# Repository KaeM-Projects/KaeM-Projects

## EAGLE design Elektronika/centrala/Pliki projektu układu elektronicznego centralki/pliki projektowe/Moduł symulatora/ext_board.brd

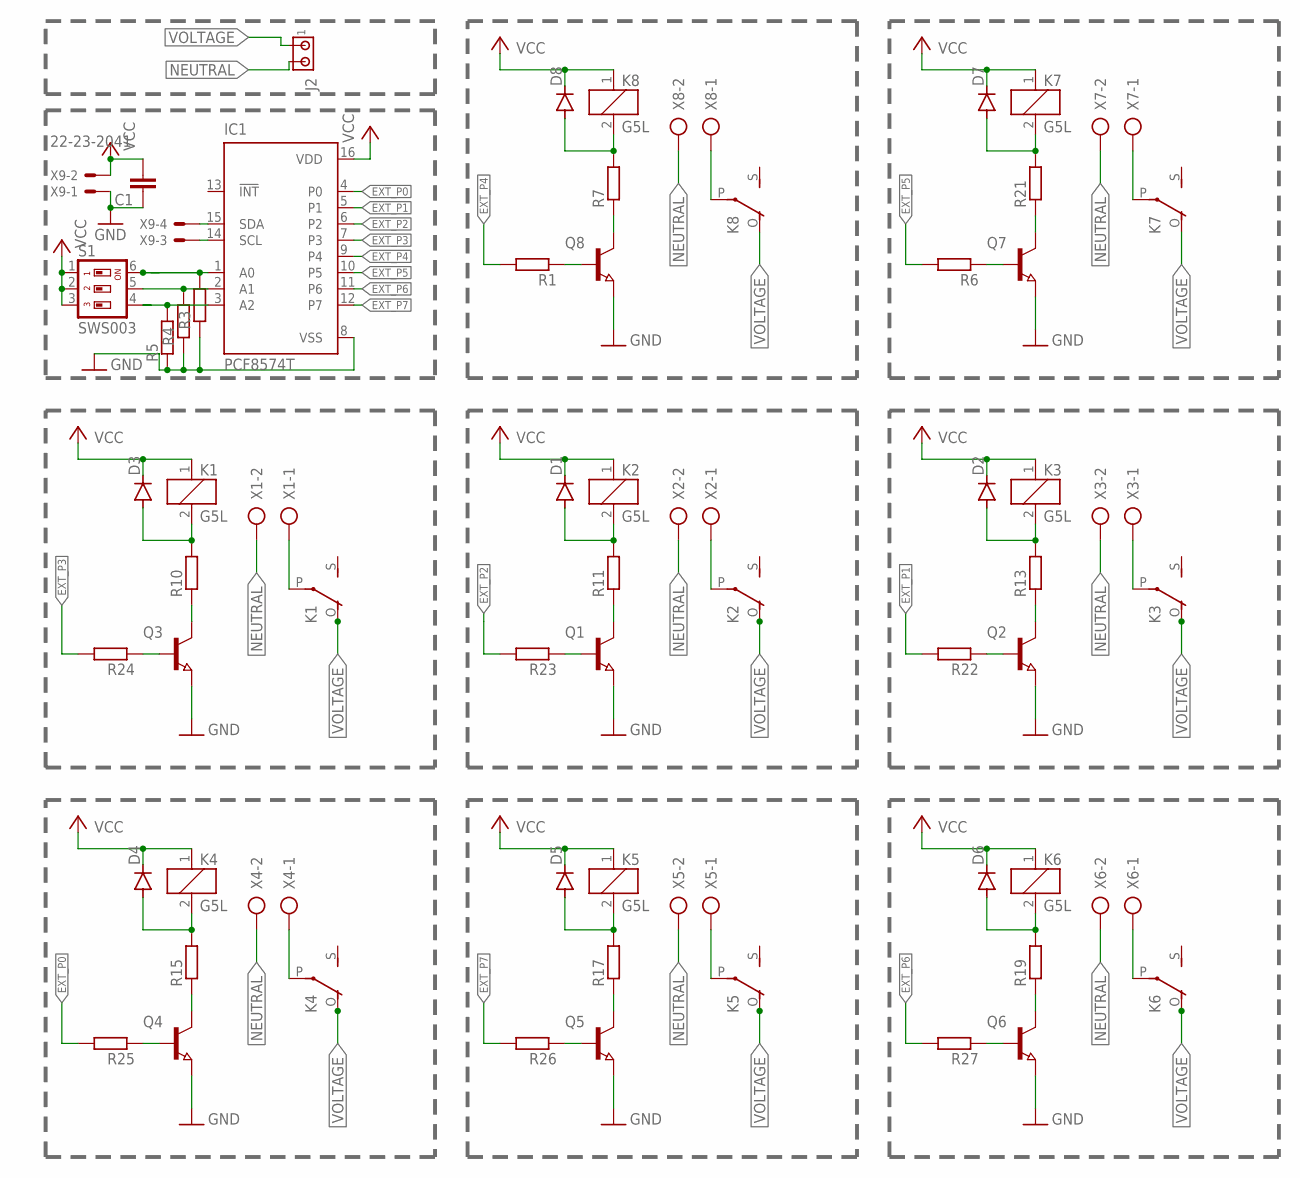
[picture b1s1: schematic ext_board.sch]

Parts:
C1: C-EUC2012; C2012
D1, D2, D3, D4, D5, D6, D7, D8: DIODE-DO-214AC; DO-214AC
IC1: PCF8574T; SO16W
J2: MTA02-156; 1X2MTA
K1, K2, K3, K4, K5, K6, K7, K8: G5L; G5LE
Q1, Q2, Q3, Q4, Q5, Q6, Q7, Q8: NPN-TRANSISTOR_SOT23; SOT23
R1, R6, R22, R23, R24, R25, R26, R27: R-EU_R2010; R2010
R3, R4, R5, R7, R10, R11, R13, R15, R17, R19, R21: R-EU_M2012; M2012
S1: SWS003; SMS-003
X1, X2, X3, X4, X5, X6, X7, X8: AK300/2
X9: 22-23-2041

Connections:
EXT_P0: IC1.4 (P0), R25.2
EXT_P1: IC1.5 (P1), R22.2
EXT_P2: IC1.6 (P2), R23.2
EXT_P3: IC1.7 (P3), R24.2
EXT_P4: IC1.9 (P4), R1.2
EXT_P5: IC1.10 (P5), R6.2
EXT_P6: IC1.11 (P6), R27.2
EXT_P7: IC1.12 (P7), R26.2
GND: C1.1, IC1.8 (VSS), Q1.2 (E), Q2.2 (E), Q3.2 (E), Q4.2 (E), Q5.2 (E), Q6.2 (E), Q7.2 (E), Q8.2 (E), R3.1, R4.1, R5.1, X9.1
unnamed: IC1.2 (A1), R4.2, S1.5
unnamed: IC1.3 (A2), R5.2, S1.4
unnamed: IC1.1 (A0), R3.2, S1.6
unnamed: Q3.1 (B), R24.1
unnamed: Q1.1 (B), R23.1
unnamed: D3.A, K1.2, R10.2
unnamed: Q3.3 (C), R10.1
unnamed: K1.P, X1.1
unnamed: D1.A, K2.2, R11.2
unnamed: Q1.3 (C), R11.1
unnamed: K2.P, X2.1
unnamed: Q2.1 (B), R22.1
unnamed: D2.A, K3.2, R13.2
unnamed: Q2.3 (C), R13.1
unnamed: K3.P, X3.1
unnamed: Q4.1 (B), R25.1
unnamed: D4.A, K4.2, R15.2
unnamed: Q4.3 (C), R15.1
unnamed: K4.P, X4.1
unnamed: Q5.1 (B), R26.1
unnamed: D5.A, K5.2, R17.2
unnamed: Q5.3 (C), R17.1
unnamed: K5.P, X5.1
unnamed: Q6.1 (B), R27.1
unnamed: D6.A, K6.2, R19.2
unnamed: Q6.3 (C), R19.1
unnamed: K6.P, X6.1
unnamed: Q7.1 (B), R6.1
unnamed: D7.A, K7.2, R21.2
unnamed: Q7.3 (C), R21.1
unnamed: K7.P, X7.1
unnamed: Q8.1 (B), R1.1
unnamed: D8.A, K8.2, R7.2
unnamed: Q8.3 (C), R7.1
unnamed: K8.P, X8.1
NEUTRAL: J2.2, X1.2, X2.2, X3.2, X4.2, X5.2, X6.2, X7.2, X8.2
SCL: IC1.14 (SCL), X9.3
SDA: IC1.15 (SDA), X9.4
VCC: C1.2, D1.C, D2.C, D3.C, D4.C, D5.C, D6.C, D7.C, D8.C, IC1.16 (VDD), K1.1, K2.1, K3.1, K4.1, K5.1, K6.1, K7.1, K8.1, S1.1, S1.2, S1.3, X9.2
VOLTAGE: J2.1, K1.O, K2.O, K3.O, K4.O, K5.O, K6.O, K7.O, K8.O

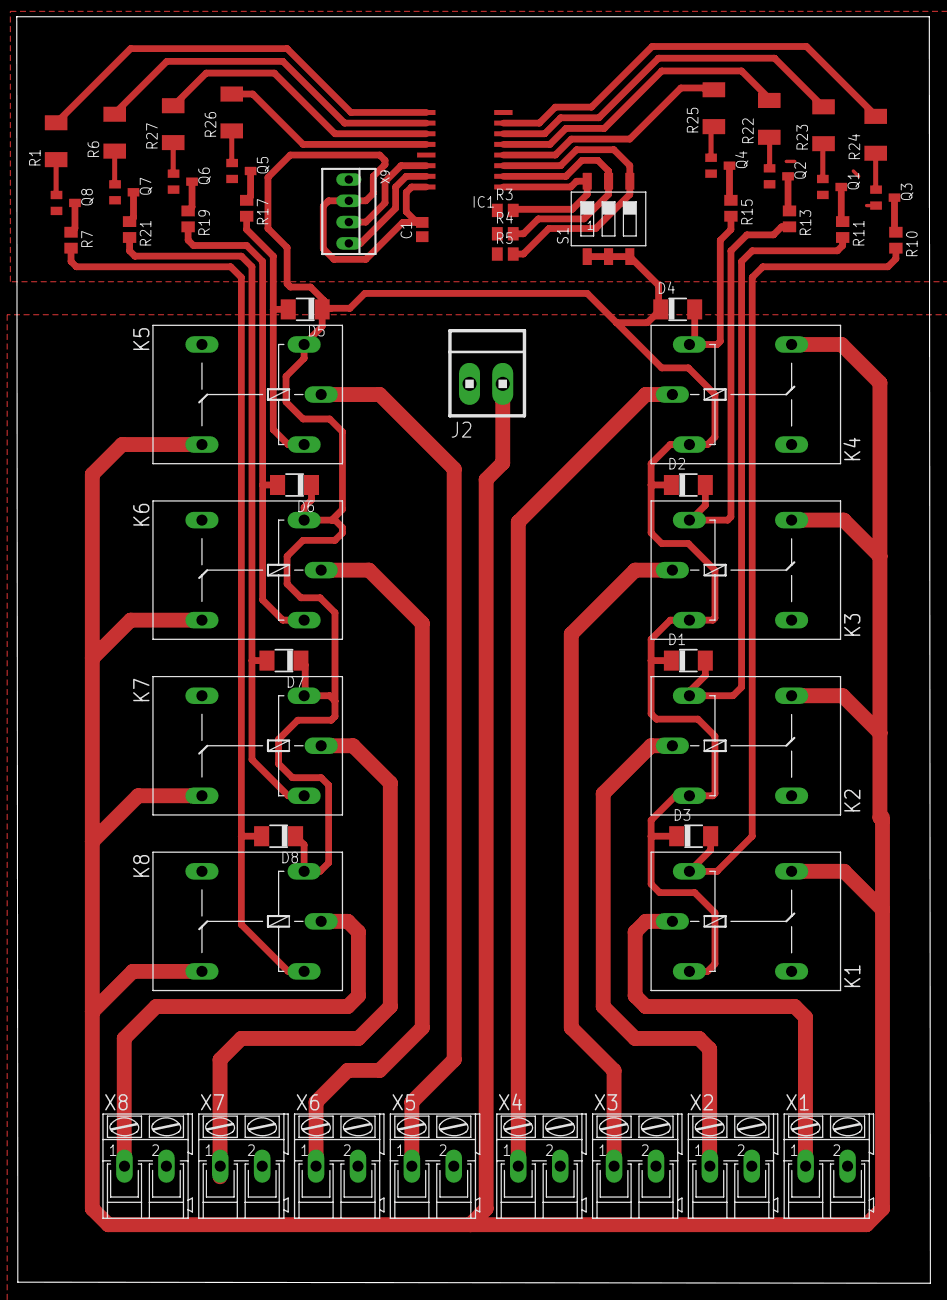
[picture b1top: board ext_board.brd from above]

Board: 2 copper layers, 109.0 x 151.1 mm, 56 parts (0 on the bottom side), 49 nets.

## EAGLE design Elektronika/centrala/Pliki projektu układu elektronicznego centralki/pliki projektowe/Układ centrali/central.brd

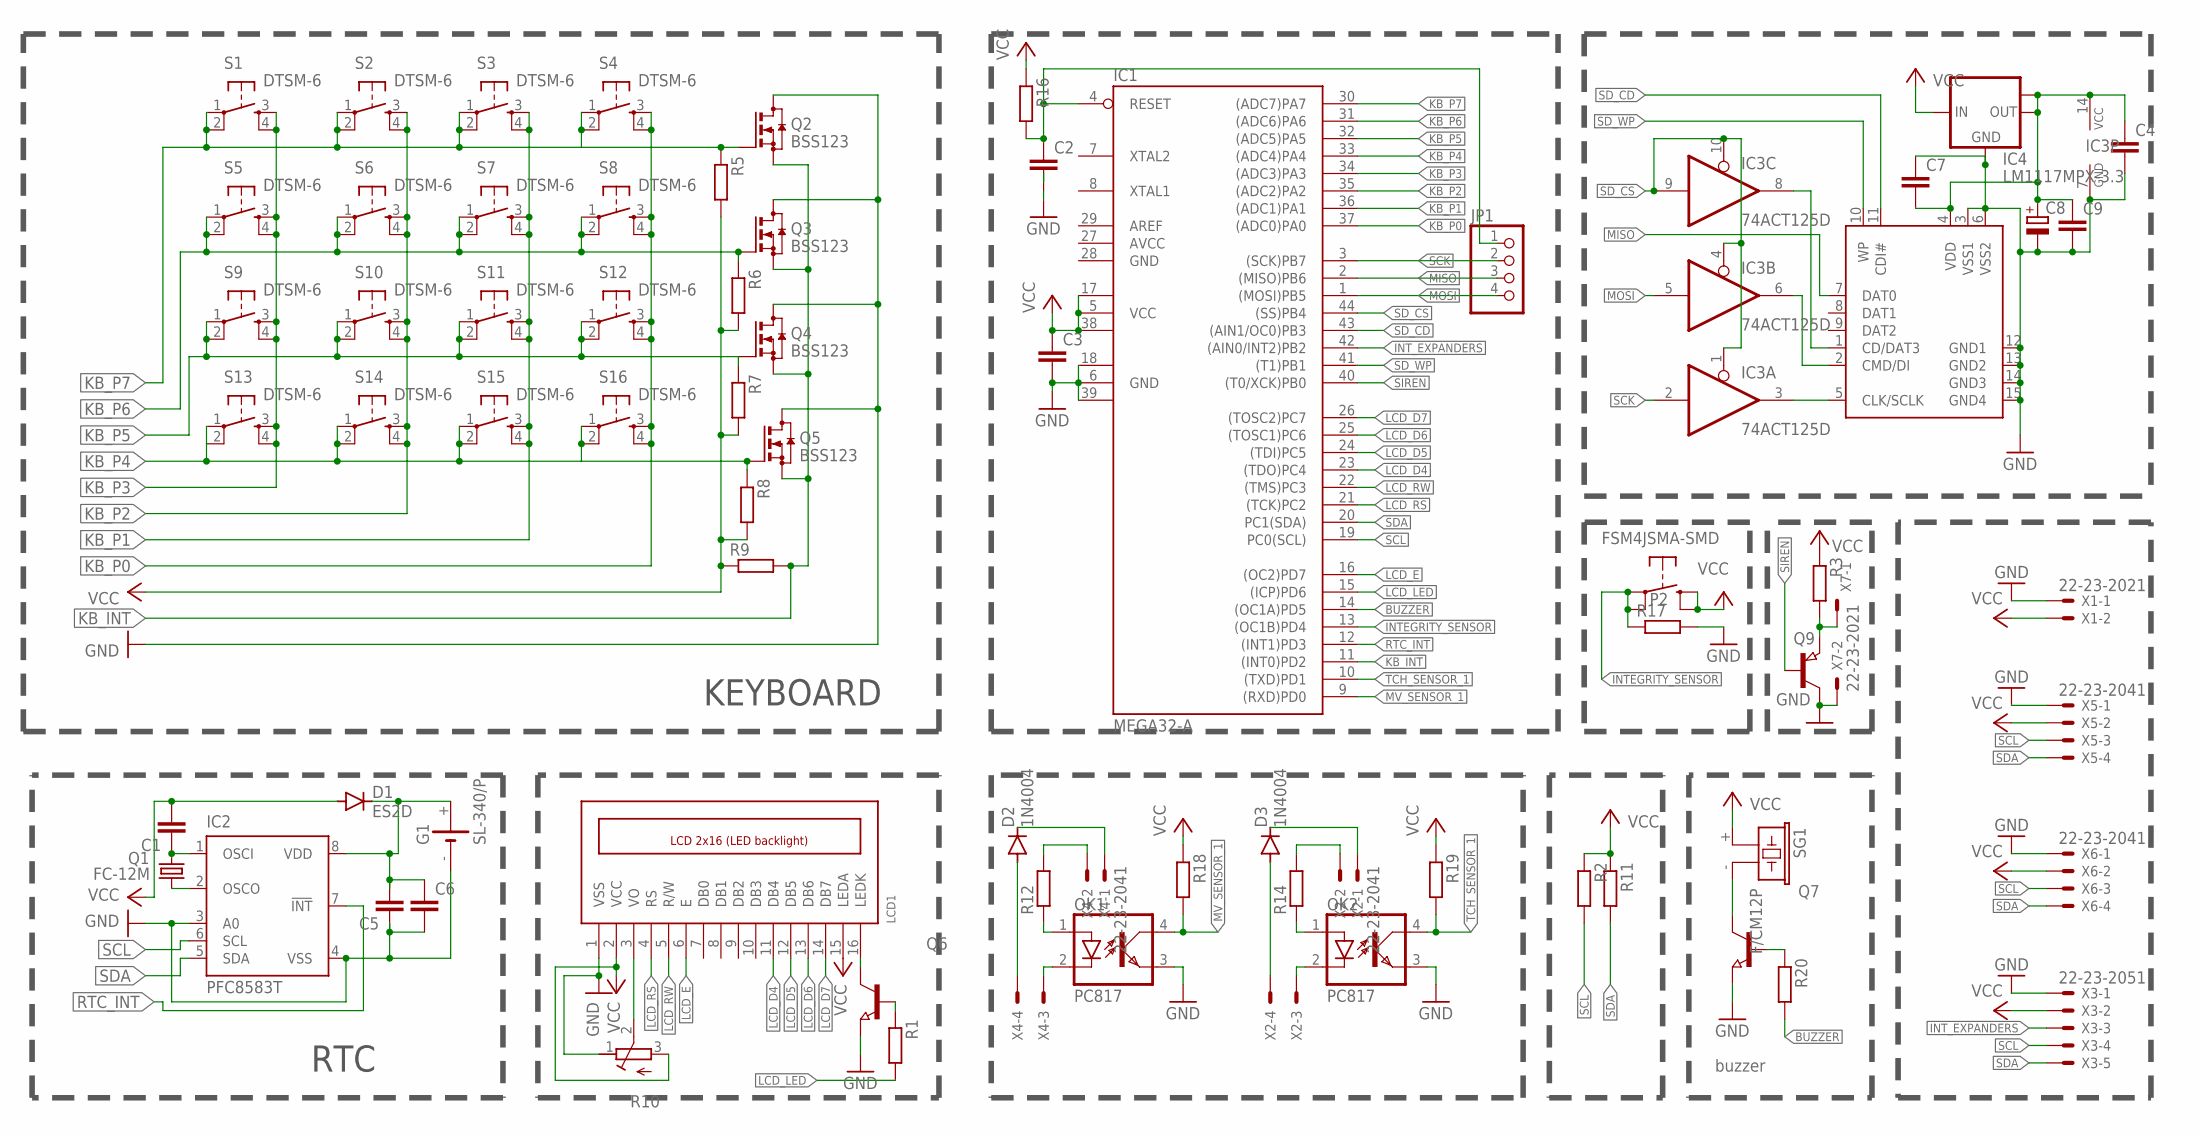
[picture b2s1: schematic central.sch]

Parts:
C1, C2, C3, C5: C-EUC2012; C2012
C4, C6, C7, C9: C-EUC4532; C4532
C8: CPOL-EUE1.8-4; E1,8-4
D1: ES2D; SMB
D2, D3: 1N4004; DO41-10
G1: SL-340/P; BEL/P
IC1: MEGA32-A; TQFP44
IC2: PFC8583T; SO8-7_5
IC3: 74ACT125D; SO14
IC4: LM1117MPX-3.3; SOT223
JP1: PINHD-1X4/90; 1X04/90
LCD1: LCD_2X16_SIL; HY-1602F
OK1, OK2: PC817; DIL04
P2: FSM4JSMA-SMD
Q1: FC-12M
Q2, Q3, Q4, Q5: BSS123; SOT23
Q6, Q7: NPN-TRANSISTOR_SOT23; SOT23
Q9: PNP-TRANSISTOR_SOT23; SOT23
R1, R2, R3, R5, R6, R7, R8, R9, R11, R16, R17, R18, R19, R20: R-EU_M3216; M3216
R10: R-TRIMM3314G; RTRIM3314G
R12, R14: R-EU_0309/12; 0309/12
S1, S2, S3, S4, S5, S6, S7, S8, S9, S10, S11, S12, S13, S14, S15, S16: DTSM-6
SG1: F/CM12P
U$1: SDCARDVAR1; SDCMF-10915W010
X1, X7: 22-23-2021
X2, X4, X5, X6: 22-23-2041
X3: 22-23-2051

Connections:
AVCC: IC1.27 (AVCC)
BUZZER: IC1.14 ((OC1A)PD5), R20.2
GND: C2.2, C3.2, C4.2, C5.1, C6.2, C7.1, C8.-, C9.2, G1.-, IC1.6 (GND), IC1.18 (GND1), IC1.28 (GND), IC1.39 (GND2), IC2.3 (A0), IC2.4 (VSS), IC3.7 (GND), IC4.1 (GND), LCD1.1 (VSS), OK1.3 (EMIT), OK2.3 (EMIT), Q2.3 (D), Q3.3 (D), Q4.3 (D), Q5.3 (D), Q6.2 (E), Q7.2 (E), Q9.3 (C), R10.1 (E), R17.2, U$1.3 (VSS1), U$1.6 (VSS2), U$1.12 (GND1), U$1.13 (GND2), U$1.14 (GND3), U$1.15 (GND4), X1.1, X3.1, X5.1, X6.1, X7.2
INTEGRITY_SENSOR: IC1.13 ((OC1B)PD4), P2.P$1, P2.P$2, R17.1
INT_EXPANDERS: IC1.42 ((AIN0/INT2)PB2), X3.3
KB_INT: IC1.11 ((INT0)PD2), Q2.2 (S), Q3.2 (S), Q4.2 (S), Q5.2 (S), R9.2
KB_P0: IC1.37 ((ADC0)PA0), S4.3, S4.4, S8.3, S8.4, S12.3, S12.4, S16.3, S16.4
KB_P1: IC1.36 ((ADC1)PA1), S3.3, S3.4, S7.3, S7.4, S11.3, S11.4, S15.3, S15.4
KB_P2: IC1.35 ((ADC2)PA2), S2.3, S2.4, S6.3, S6.4, S10.3, S10.4, S14.3, S14.4
KB_P3: IC1.34 ((ADC3)PA3), S1.3, S1.4, S5.3, S5.4, S9.3, S9.4, S13.3, S13.4
KB_P4: IC1.33 ((ADC4)PA4), Q5.1 (G), R8.1, S13.1, S13.2, S14.1, S14.2, S15.1, S15.2, S16.1, S16.2
KB_P5: IC1.32 ((ADC5)PA5), Q4.1 (G), R7.1, S9.1, S9.2, S10.1, S10.2, S11.1, S11.2, S12.1, S12.2
KB_P6: IC1.31 ((ADC6)PA6), Q3.1 (G), R6.1, S5.1, S5.2, S6.1, S6.2, S7.1, S7.2, S8.1, S8.2
KB_P7: IC1.30 ((ADC7)PA7), Q2.1 (G), R5.1, S1.1, S1.2, S2.1, S2.2, S3.1, S3.2, S4.1, S4.2
LCD_D4: IC1.23 ((TDO)PC4), LCD1.11 (DB4)
LCD_D5: IC1.24 ((TDI)PC5), LCD1.12 (DB5)
LCD_D6: IC1.25 ((TOSC1)PC6), LCD1.13 (DB6)
LCD_D7: IC1.26 ((TOSC2)PC7), LCD1.14 (DB7)
LCD_E: IC1.16 ((OC2)PD7), LCD1.6 (E)
LCD_LED: IC1.15 ((ICP)PD6), R1.2
LCD_RS: IC1.21 ((TCK)PC2), LCD1.4 (RS)
LCD_RW: IC1.22 ((TMS)PC3), LCD1.5 (R/W)
MISO: IC1.2 ((MISO)PB6), JP1.3, U$1.7 (DAT0)
MOSI: IC1.1 ((MOSI)PB5), IC3.5 (I), JP1.4
MV_SENSOR_1: IC1.9 ((RXD)PD0), OK1.4 (COL), R18.2
unnamed: C1.1, IC2.1 (OSCI), Q1.2
unnamed: IC2.2 (OSCO), Q1.1
unnamed: D2.A, X4.4
unnamed: D3.A, X2.4
unnamed: C5.2, C6.1, D1.C, G1.+, IC2.8 (VDD)
unnamed: LCD1.16 (LEDK), Q6.3 (C)
unnamed: OK1.2 (C), X4.3
unnamed: R12.2, X4.2
unnamed: D2.C, X4.1
unnamed: OK2.2 (C), X2.3
unnamed: R14.2, X2.2
unnamed: D3.C, X2.1
unnamed: Q7.3 (C), SG1.- (2)
unnamed: LCD1.3 (VO), R10.2 (S)
unnamed: Q7.1 (B), R20.1
unnamed: C2.1, IC1.4 (RESET), JP1.1, R16.2
unnamed: Q6.1 (B), R1.1
unnamed: IC3.3 (O), U$1.5 (CLK/SCLK)
unnamed: OK2.1 (A), R14.1
unnamed: IC3.6 (O), U$1.2 (CMD/DI)
unnamed: OK1.1 (A), R12.1
unnamed: Q9.2 (E), R3.2, X7.1
unnamed: IC3.8 (O), U$1.1 (CD/DAT3)
unnamed: C4.1, C7.2, C8.+, C9.1, IC3.14 (VCC), IC4.2 (OUT), IC4.TAB (OUT1), U$1.4 (VDD)
RTC_INT: IC1.12 ((INT1)PD3), IC2.7 (!INT)
SCK: IC1.3 ((SCK)PB7), IC3.2 (I), JP1.2
SCL: IC1.19 (PC0(SCL)), IC2.6 (SCL), R2.2, X3.4, X5.3, X6.3
SDA: IC1.20 (PC1(SDA)), IC2.5 (SDA), R11.2, X3.5, X5.4, X6.4
SD_CD: IC1.43 ((AIN1/OC0)PB3), U$1.11 (CDI#)
SD_CS: IC1.44 ((SS)PB4), IC3.1 (OE), IC3.4 (OE), IC3.9 (I), IC3.10 (OE)
SD_WP: IC1.41 ((T1)PB1), U$1.10 (WP)
SIREN: IC1.40 ((T0/XCK)PB0), Q9.1 (B)
TCH_SENSOR_1: IC1.10 ((TXD)PD1), OK2.4 (COL), R19.2
VCC: C1.2, C3.1, D1.A, IC1.5 (VCC), IC1.17 (VCC1), IC1.38 (VCC2), IC4.3 (IN), LCD1.2 (VCC), LCD1.15 (LEDA), P2.P$3 (S), P2.P$4 (S), R2.1, R3.1, R5.2, R6.2, R7.2, R8.2, R9.1, R10.3 (A), R11.1, R16.1, R18.1, R19.1, SG1.+ (1), X1.2, X3.2, X5.2, X6.2

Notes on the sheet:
KEYBOARD
RTC
buzzer

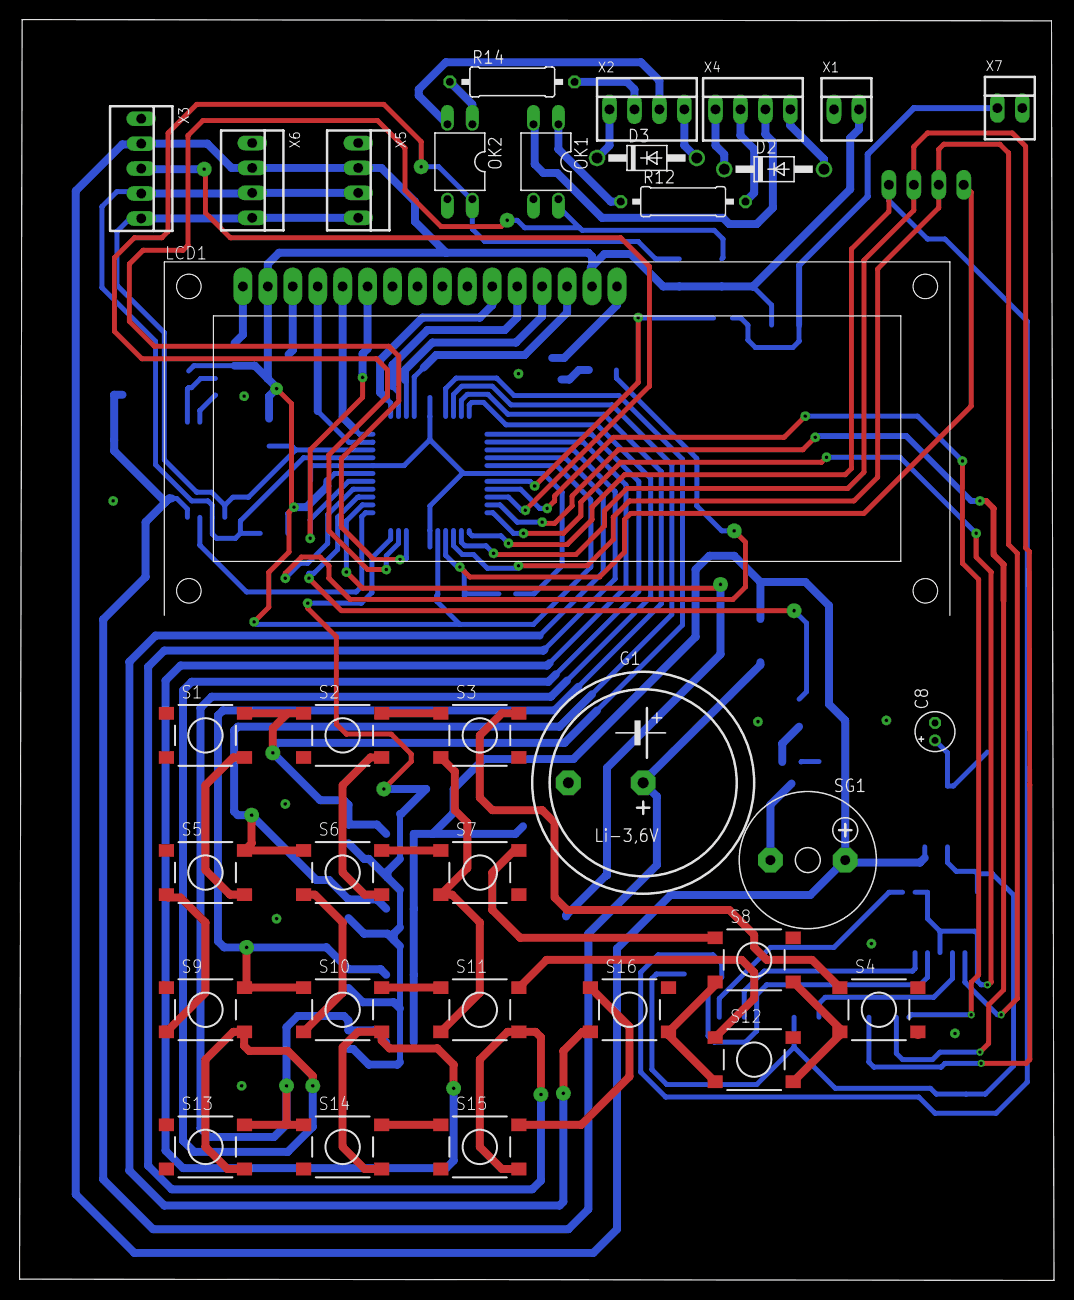
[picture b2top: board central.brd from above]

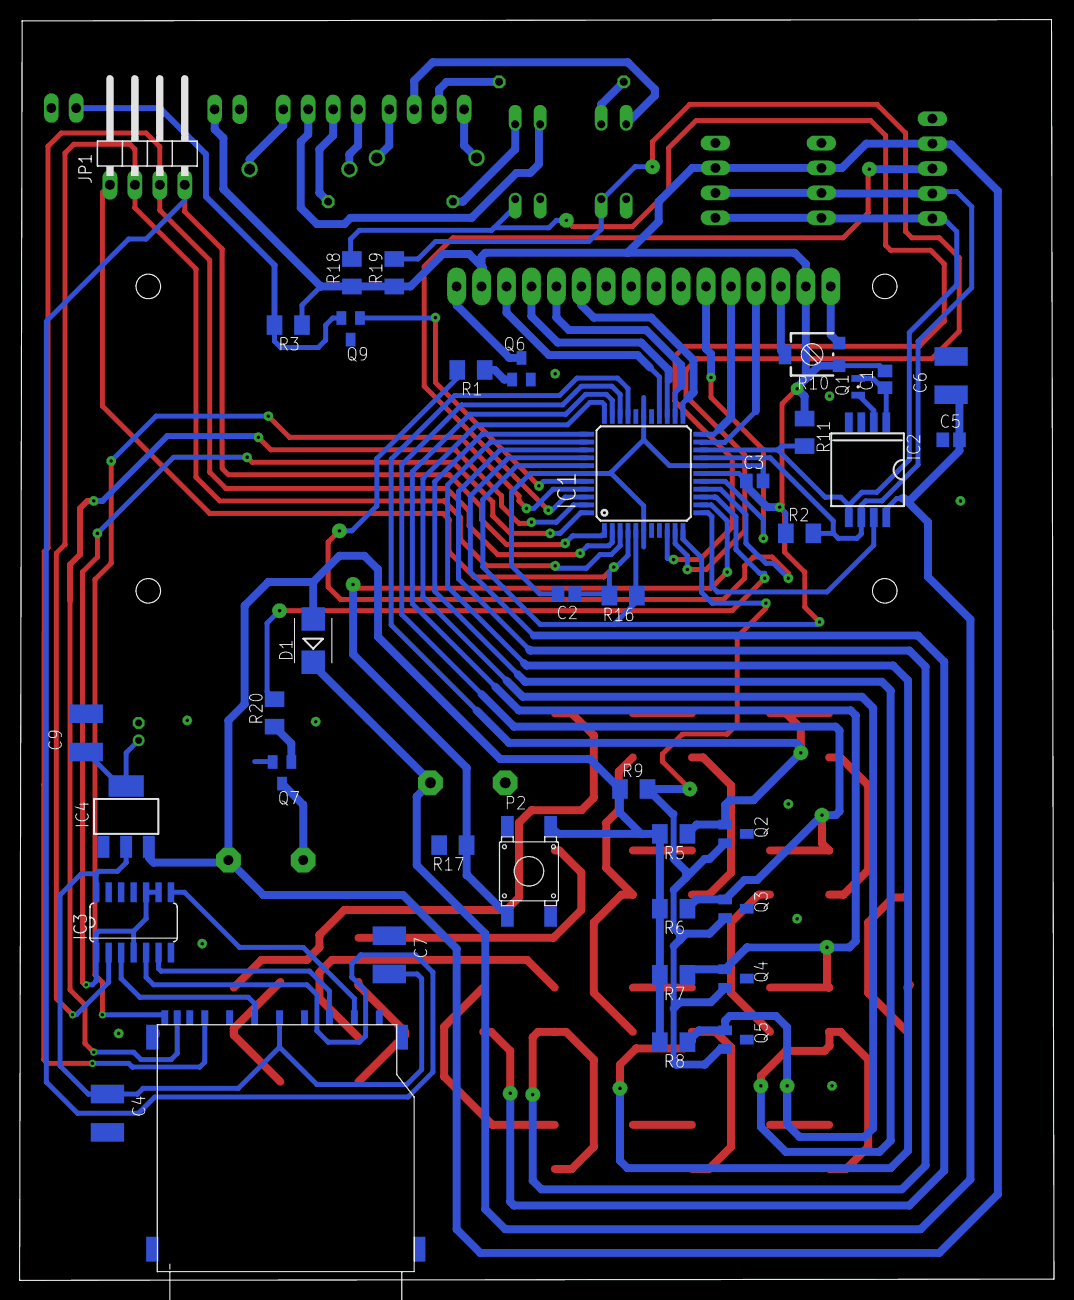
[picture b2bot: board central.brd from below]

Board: 2 copper layers, 105.3 x 128.4 mm, 72 parts (39 on the bottom side), 58 nets.

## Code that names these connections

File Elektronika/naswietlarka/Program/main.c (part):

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#define par_MAX 59

//przycisk 1 wartoci zwiêksz							
#define pin_przycisk_1 (1<<PC7)
#define przycisk_1 !(PINC & pin_przycisk_1)

//przycisk 2 wartoci zmniejsz
#define pin_przycisk_2 (1<<PC6)
#define przycisk_2 !(PINC & pin_przycisk_2)

//przycisk 3 funkcyjny
#define pin_przycisk_3 (1<<PC5)
#define przycisk_3 !(PINC & pin_przycisk_3)

//przycisk 4 start/pauza
#define pin_przycisk_4 (1<<PC4)
#define przycisk_4 !(PINC & pin_przycisk_4)

//przycisk 5 stop
#define pin_przycisk_5 (1<<PC3)
#define przycisk_5 !(PINC & pin_przycisk_5)

//przycisk 6 wiat³o w³¹cz wy³¹cz poza odliczaniem
#define pin_przycisk_6 (1<<PC2)
#define przycisk_6 !(PINC & pin_przycisk_6)



//wiate³o
#define pin_swiatlo (1<<PC1)
#define swiatlo_on PORTC &= ~pin_swiatlo
#define swiatlo_off PORTC |= pin_swiatlo

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#define od_tylu_zliczaj 9000	//od tylu zaczynaj nastêpne czekanie


#define pin_pikaczu (1<<PC0)	//definicja pinu i wartoci g³ociczka
#define pikaczu_on PORTC |= pin_pikaczu
#define pikaczu_off PORTC &= ~pin_pikaczu

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
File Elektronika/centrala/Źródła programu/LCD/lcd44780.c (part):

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
// makrodefinicje operacji na sygna³ach steruj¹cych RS,RW oraz E

#define SET_RS 	PORT(LCD_RSPORT) |= (1<<LCD_RS)			// stan wysoki na linii RS
#define CLR_RS 	PORT(LCD_RSPORT) &= ~(1<<LCD_RS)		// stan niski na linii RS

#define SET_RW 	PORT(LCD_RWPORT) |= (1<<LCD_RW)			// stan wysoki na RW - odczyt z LCD
#define CLR_RW 	PORT(LCD_RWPORT) &= ~(1<<LCD_RW)		// stan niski na RW - zapis do LCD

#define SET_E 	PORT(LCD_EPORT) |= (1<<LCD_E)			// stan wysoki na linii E
#define CLR_E 	PORT(LCD_EPORT) &= ~(1<<LCD_E)			// stan niski na linii E

uint8_t check_BF(void);			// deklaracja funkcji wewnêtrznej

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{
	uint8_t result=0;

	if(PIN(LCD_D4PORT)&(1<<LCD_D4)) result |= (1<<0);
	if(PIN(LCD_D5PORT)&(1<<LCD_D5)) result |= (1<<1);
	if(PIN(LCD_D6PORT)&(1<<LCD_D6)) result |= (1<<2);
	if(PIN(LCD_D7PORT)&(1<<LCD_D7)) result |= (1<<3);

	return result;
}
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
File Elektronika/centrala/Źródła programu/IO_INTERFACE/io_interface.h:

#ifndef IO_INTERFACE_IO_INTERFACE_H_
#define IO_INTERFACE_IO_INTERFACE_H_

#define SENSOR_1_PORT D
#define SENSOR_1_PIN 0

#define SENSOR_2_PORT D
#define SENSOR_2_PIN 1

#define INTEGRITY_SENSOR_PORT D
#define INTEGRITY_SENSOR_PIN 4

#define SIREN_PORT B
#define SIREN_PIN 0
#define SIREN_ON PORT(SIREN_PORT) |= (1<<SIREN_PIN)
#define SIREN_OFF PORT(SIREN_PORT) &= (1<<SIREN_PIN)

#define INTEGRITY_SENSOR_IN DDR(INTEGRITY_SENSOR_PORT) &= ~(1<<INTEGRITY_SENSOR_PIN)
#define INTEGRITY_SENSOR_LOW PORT(INTEGRITY_SENSOR_PORT) &= ~(1<<INTEGRITY_SENSOR_PIN)
#define INTEGRITY_SENSOR PIN(INTEGRITY_SENSOR_PORT) & (1<<INTEGRITY_SENSOR_PIN)
#define INTEGRITY_SENSOR_TRIGGERED !(INTEGRITY_SENSOR)

#define SENSOR_1_IN DDR(SENSOR_1_PORT) &= ~(1<<SENSOR_1_PIN)
#define SENSOR_1_LOW PORT(SENSOR_1_PORT) &= ~(1<<SENSOR_1_PIN)
#define SENSOR_1 PIN(SENSOR_1_PORT) & (1<<SENSOR_1_PIN)
#define SENSOR_1_TRIGGERED !(SENSOR_1)

#define SENSOR_2_IN DDR(SENSOR_2_PORT) &= ~(1<<SENSOR_2_PIN)
#define SENSOR_2_LOW PORT(SENSOR_2_PORT) &= ~(1<<SENSOR_2_PIN)
#define SENSOR_2 PIN(SENSOR_2_PORT) & (1<<SENSOR_2_PIN)
#define SENSOR_2_TRIGGERED !(SENSOR_2)

#define PORT(x) SPORT(x)
#define SPORT(x) (PORT##x)
// *** PIN
#define PIN(x) SPIN(x)
#define SPIN(x) (PIN##x)
// *** DDR
#define DDR(x) SDDR(x)
#define SDDR(x) (DDR##x)

#define PCF8574_1_ADDR 0x40
#define out_module_1 PCF8574_1_ADDR

#define SD_CD (1<<PB3)
#define SD_CD_set_in (DDRB &= ~SD_CD)
#define SD_CD_pull_up (PORTB |= SD_CD)
#define SD_CD_status !(PINB & SD_CD)

#define buzzer_pin (1<<PD5)
#define buzzer_as_out (DDRD |= buzzer_pin)
#define buzzer_off (PORTD &= ~buzzer_pin)
#define buzzer_on (PORTD |= buzzer_pin)

typedef enum{WRONG, CORRECT, TIME_SEC, BUTTON}buzz_type;
typedef enum {sim_module_1}modules;

void SD_init(void);
void sensors_initialize(void);
void set_out_module(uint8_t module, uint8_t value);
void buzzer(buzz_type buzz);

volatile uint8_t buzzer_time;
volatile uint8_t buzzer_pause;
volatile uint8_t buzzer_cnt;
volatile BOOL buzzer_start;
volatile uint8_t buzzer_delay;

#endif /* IO_INTERFACE_IO_INTERFACE_H_ */

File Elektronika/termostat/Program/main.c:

#include <avr/io.h>
#include <util/delay.h>
#include <avr/interrupt.h>
#include "7_segm.h"
#include "zegar.h"
#include "ds18x20.h"

#define temp_MIN 10
#define temp_MAX 120
#define BLAD 3

//przycisk 1 temp w górê
#define pin_przycisk_1 (1<<PC7)
#define przycisk_1 !(PINC & pin_przycisk_1)

//przycisk 2 temp w dó³
#define pin_przycisk_2 (1<<PC6)
#define przycisk_2 !(PINC & pin_przycisk_2)

#define pin_przycisk_3 (1<<PC5)
#define przycisk_3 !(PINC & pin_przycisk_3)

#define czekaj_tyle 5000		//czekaj tyle przy wcinietym przycisku
#define od_tylu_zliczaj 4500

#define pin_pikaczu (1<<PC0)
#define pikaczu_on PORTC |= pin_pikaczu
#define pikaczu_off PORTC &= ~pin_pikaczu

#define pin_grzalka (1<<PB7)
#define grzalka_off PORTB |= pin_grzalka
#define grzalka_on PORTB &= ~pin_grzalka

#define pin_gotowy_led (1<<PB5)
#define gotowy_led_off PORTB |= pin_gotowy_led
#define gotowy_led_on PORTB &= ~pin_gotowy_led 


uint8_t	tab_temp[3];
uint8_t temp = temp_MIN;
uint8_t a = 1;
// zmienne dla przycisków


uint8_t czujniki_cnt;
uint8_t subzero, cel, cel_frac_bits;
uint8_t wynik, popr = 0;
uint8_t temp_rob = temp_MIN;
uint8_t cnt250ms = 0;
uint8_t pol_sec = 0;
uint8_t zakres_1;
uint8_t zakres_2;
uint8_t pszy_raz = 0;
////////////


//////////// funkcje
void zmiana_parametrow()
{

	uint8_t i;
	
	for(i=0; i<=2; i++)
		{
			tab_temp[i]=temp_rob%10;
			temp_rob /=10;
   		}	

	zakres_1 = (temp - 9);
	zakres_2 = (temp - 4);	
			
		if (popr)
		{
			if (tab_temp[2]>0) wysw_1 = tab_temp[2];
			else wysw_1 = NIC;
   			wysw_2 = tab_temp[1];
   			wysw_3 = tab_temp[0];
			wysw_4 = 10;
			wysw_5 = 11;
		}
		else
		{

			if(flaga_250ms_2)
			{
				if (pol_sec > 4) pol_sec = 0;		

				if (pol_sec <= 2)
				{
					if (tab_temp[2]>0) wysw_1 = tab_temp[2];
					else wysw_1 = NIC;
   					wysw_2 = tab_temp[1];
   					wysw_3 = tab_temp[0];
					wysw_4 = 10;
					wysw_5 = 11;
				}
				if (pol_sec > 2 )
				{
					wysw_1 = NIC;
					wysw_2 = E;
					wysw_3 = r;
					wysw_4 = r;
					wysw_5 = NIC;
				}
	
				pol_sec++;
				flaga_250ms_2 = 0;
			}
			

		}
}

///////////////////////////////////////////////////////////

void zwieksz_temp()
{
	if (temp<temp_MAX) 
	{
		temp++;
		a=1;
	}
	else 
	{
		if (a)
		{
			temp = temp_MAX;
			uint16_t j,k;
			for(k=0; k<=1; k++)
			{
				for(j=0; j<=5000; j++)
				{
					pikaczu_on;
		
				}
				for(j=0; j<=5000; j++)
				{
					pikaczu_off;
		
				}
			}
			a=0;
		}
	}
	temp_rob = temp;
	zmiana_parametrow();
}

//////////////////////////////////////////////////////////////////

void zmniejsz_temp()
{
	if (temp>temp_MIN)
		{
			temp--;
			a=1;
		}
	else 
	{
		if (a)
	{
		temp = temp_MIN;
		uint16_t j,k;
		for(k=0; k<=1; k++)
		{
			for(j=0; j<=5000; j++)
			{
				pikaczu_on;
		
			}

			for(j=0; j<=5000; j++)
			{
				pikaczu_off;
		
			}
		}
		a=0;
		}		
	}
	temp_rob = temp;
	zmiana_parametrow();

}

/////////////////////////////////////////////////////////////////////

void wyswietl_bierzaca()
{

	if (popr)
		{
			temp_rob = wynik;
			zmiana_parametrow();
		}
	else
		{
			wysw_1 = NIC;
			wysw_2 = E;
			wysw_3 = r;
			wysw_4 = r;
			wysw_5 = NIC;
		}


}


void grzalka()
{

	if (popr) 
	{
		if (wynik < zakres_1) grzalka_on;

		if ((wynik >= zakres_1) && (wynik <= zakres_2))
		{
			if (sekundy <= 4) grzalka_on;
			else grzalka_off;
		
		}

		if ((wynik > zakres_2) && (wynik < temp))
		{
			if (sekundy <= 2) grzalka_on;
			else grzalka_off;
		}

	

	
		if (wynik == temp)
			{
				if (sekundy <= 1) grzalka_on;
				else grzalka_off;
		
			}

		if (wynik > temp) grzalka_off;

	}
	else grzalka_off;

}

void gotowy()
{
	if ((wynik == temp) && !pszy_raz) 
	{
		gotowy_led_on;
		
	}
	if ((wynik - BLAD) == temp || (wynik + BLAD) == temp)
	{
	gotowy_led_off;
	pszy_raz = 0;
	}


}


void inicjalizacja_czujnika()
{

	czujniki_cnt = search_sensors();

	DS18X20_start_meas(DS18X20_POWER_EXTERN, NULL);

	_delay_ms(750);

	if (DS18X20_OK == DS18X20_read_meas_single( 0x28 , &subzero, &cel, &cel_frac_bits))
	{
	popr = 1;
	wynik = cel;
	}
		else popr = 0;

	_delay_ms(250);
}

///////////////////////////////////


int main(void)
{

uint8_t zatrzask = 0;
uint8_t zatrzask_2 = 0;
uint8_t zatrzask_3 = 0;
uint16_t staly = 0;				//kontrolka wcisku sta³ego
uint16_t staly_2 = 0;
uint8_t powroc = 0;
uint8_t bierz = 0;


	wyswietlanie_led();
	zegar();
	sei();

	DDRC &= ~pin_przycisk_1;	//ustawianie pinów przycisków na wejciowe 
	PORTC |=pin_przycisk_1;		//i podci¹gniêcie do VCC

	DDRC &= ~pin_przycisk_2;
	PORTC |=pin_przycisk_2;

	DDRC &= ~pin_przycisk_3;
	PORTC |=pin_przycisk_3;

	DDRC |= pin_pikaczu;

	DDRB |= pin_grzalka;
	PORTB &= ~pin_grzalka;

	DDRB |= pin_gotowy_led;
	PORTB |= pin_gotowy_led;

	
	
//	

//	while (p1)
//	{

		wysw_1 = 8;
		wysw_2 = 8;
		wysw_3 = 8;
		wysw_4 = 8;
		wysw_5 = 8;

		pikaczu_on;


inicjalizacja_czujnika();

		pikaczu_off;

//		if (flaga_250ms_3)
//		{
//			p1++;
//			if (p1 == 7) p1 = 0;
//			flaga_250ms_3 = 0;
//		}
	
//	}

	zmiana_parametrow();


	while(1)
	{	
		

		if (przycisk_1 && !zatrzask)	//jeli przycisk pierwszy raz
			{
			
										//funkcja w³aciwa
				zatrzask=1;			//ustawienie zatrzasku
				staly=0;			//zerowanie kontrolki przycisku sta³ego
				zwieksz_temp();
					
						
			}


		if (!(przycisk_1) && zatrzask) 	//drgania styków
			{	
				zatrzask++;
			
			}



		if (przycisk_1 && zatrzask)		//jeli przycisk d³u¿ej wciniêty
			{
			
				
				if (staly == czekaj_tyle)		
					{
					staly = od_tylu_zliczaj;
					zwieksz_temp();
						
					}		
				staly++;
			}					
			
///////////////////////////////////////////////////zmniejszanie temp			
			
		if (przycisk_2 && !zatrzask_2)	//jeli przycisk pierwszy raz
			{
			
										//funkcja w³aciwa
				zatrzask_2=1;			//ustawienie zatrzasku
				staly_2=0;			//zerowanie kontrolki przycisku sta³ego
				zmniejsz_temp();
					
						
			}


		if (!(przycisk_2) && zatrzask_2) 	//drgania styków
			{	
				zatrzask_2++;
				
			}



		if (przycisk_2 && zatrzask_2)		//jeli przycisk d³u¿ej wciniêty
			{
			
					
				if (staly_2 == czekaj_tyle)		
					{
					staly_2 = od_tylu_zliczaj;
					zmniejsz_temp();
						
					}		
				staly_2++;
			}

/////////////////////////////////////////////////////////////////////////////


		if (przycisk_3 && !zatrzask_3)	//jeli przycisk pierwszy raz
			{
			
										//funkcja w³aciwa
				zatrzask_3=1;			//ustawienie zatrzasku
				bierz = 1;
				
					
						
			}


		if (!(przycisk_3) && zatrzask_3) 	//drgania styków
			{	
				zatrzask_3++;
				if (zatrzask_3 == 255) 
				{
					bierz = 0;
					temp_rob = temp;
					zmiana_parametrow();
				}
			}


///////////////////////////////////////////////////
		

		if (bierz) wyswietl_bierzaca();


//////////////////////////////////////////////////

		if (flaga250ms)
		{
			if (cnt250ms == 4) cnt250ms = 0;

			if (cnt250ms == 0)
			{
			//czujniki_cnt = search_sensors();
			DS18X20_start_meas(DS18X20_POWER_EXTERN, NULL);		//wysy³ ¿¹dania pomiaru
			
			}
			
			if (cnt250ms == 3)
			{
				if (DS18X20_OK == DS18X20_read_meas_single( 0x28 , &subzero, &cel, &cel_frac_bits))
				{
					popr = 1;
					wynik = cel;
				}
				else popr = 0;								//odczyt
		
			}
		cnt250ms++;
		flaga250ms = 0;

		}


	grzalka();
	gotowy();



	if (!popr) 
	{
		powroc = 1;
		temp_rob = temp;
		zmiana_parametrow();
	}
		
	if (popr && powroc) 
	{
		powroc = 0;
		temp_rob = temp;
		zmiana_parametrow();
	}




////////////////////////////////////////////////////////////////////////

	


//////////////////////////////////////////
	}  //koniec while
		
} //koniec main

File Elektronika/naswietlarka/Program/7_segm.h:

#ifndef     _7_segm_h
#define     _7_segm_h 


#define			wysw_cyfry		PORTA
#define			wysw_cyfry_kier	DDRA
#define			port_anody		PORTB
#define			anody_kier		DDRB

#define			anoda_1		(1<<PB0)
#define			anoda_2		(1<<PB1)
#define			anoda_3		(1<<PB2)
#define			anoda_4		(1<<PB3)
//#define			anoda_5		(1<<PB4)

#define SEG_A (1<<0)
#define SEG_B (1<<1)
#define SEG_C (1<<2)
#define SEG_D (1<<3)
#define SEG_E (1<<4)
#define SEG_F (1<<5)
#define SEG_G (1<<6)
#define SEG_DP (1<<7)

#define NIC 10


extern volatile uint8_t wysw_1;
extern volatile uint8_t wysw_2;
extern volatile uint8_t wysw_3;
extern volatile uint8_t wysw_4;
//extern volatile uint8_t wysw_5;



void wyswietlanie_led(void); //obszar deklaracji fukcji udostêpnionych dla innych modu³ów

#endif //koniec _d_led_h

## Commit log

2024-08-09 Portfolio added.
2025-02-06 Added Digital Verilog and SystemVerilog designs
2025-05-29 UVM simple design added
